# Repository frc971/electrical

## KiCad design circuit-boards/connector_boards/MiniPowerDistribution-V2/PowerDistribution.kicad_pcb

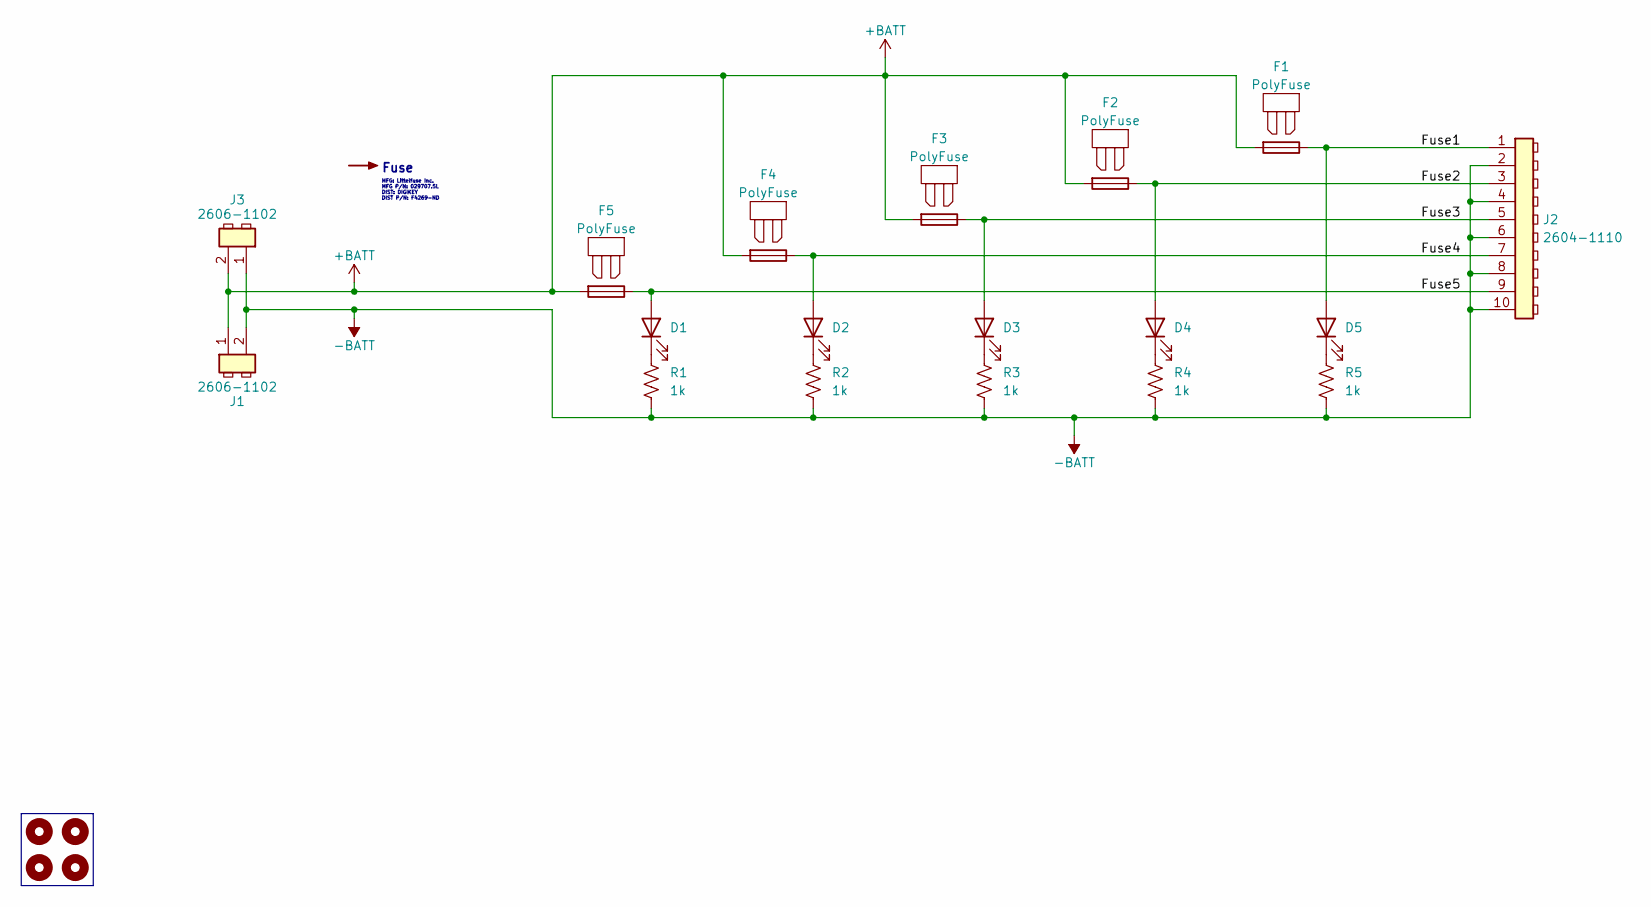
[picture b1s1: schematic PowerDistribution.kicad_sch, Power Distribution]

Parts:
D1, D2, D3, D4, D5: QTLP651C4TR; LED_1206_3216Metric_Pad1.42x1.75mm_HandSolder; MFG P/N QTLP651C4TR
F1, F2, F3, F4, F5: PolyFuse; FUSE_3568; MFG P/N 3568
H1, H2, H5, H6: MountingHole; MountingHole_2.2mm_M2_DIN965_Pad
J1, J3: 2606-1102; 2606-1102&slash_000-005; MFG P/N 2606-1102
J2: 2604-1110; MFG P/N 2604-1110
R1, R2, R3, R4, R5: 1k; R_1206_3216Metric_Pad1.30x1.75mm_HandSolder; MFG P/N RMCF1206FT1K00

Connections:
+BATT: F1.2, F2.2, F3.2, F4.2, F5.2, J1.1, J3.2
-BATT: J1.2, J2.2, J2.4, J2.6, J2.8, J2.10, J3.1, R1.2, R2.2, R3.2, R4.2, R5.2
/Fuse1: D5.2 (A), F1.1, J2.1
/Fuse2: D4.2 (A), F2.1, J2.3
/Fuse3: D3.2 (A), F3.1, J2.5
/Fuse4: D2.2 (A), F4.1, J2.7
/Fuse5: D1.2 (A), F5.1, J2.9
unnamed: D1.1 (K), R1.1
unnamed: D2.1 (K), R2.1
unnamed: D3.1 (K), R3.1
unnamed: D4.1 (K), R4.1
unnamed: D5.1 (K), R5.1

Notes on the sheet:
Fuse
MFG: Littelfuse Inc. MFG P/N: 029707.5L DIST: DIGIKEY DIST P/N: F4269-ND

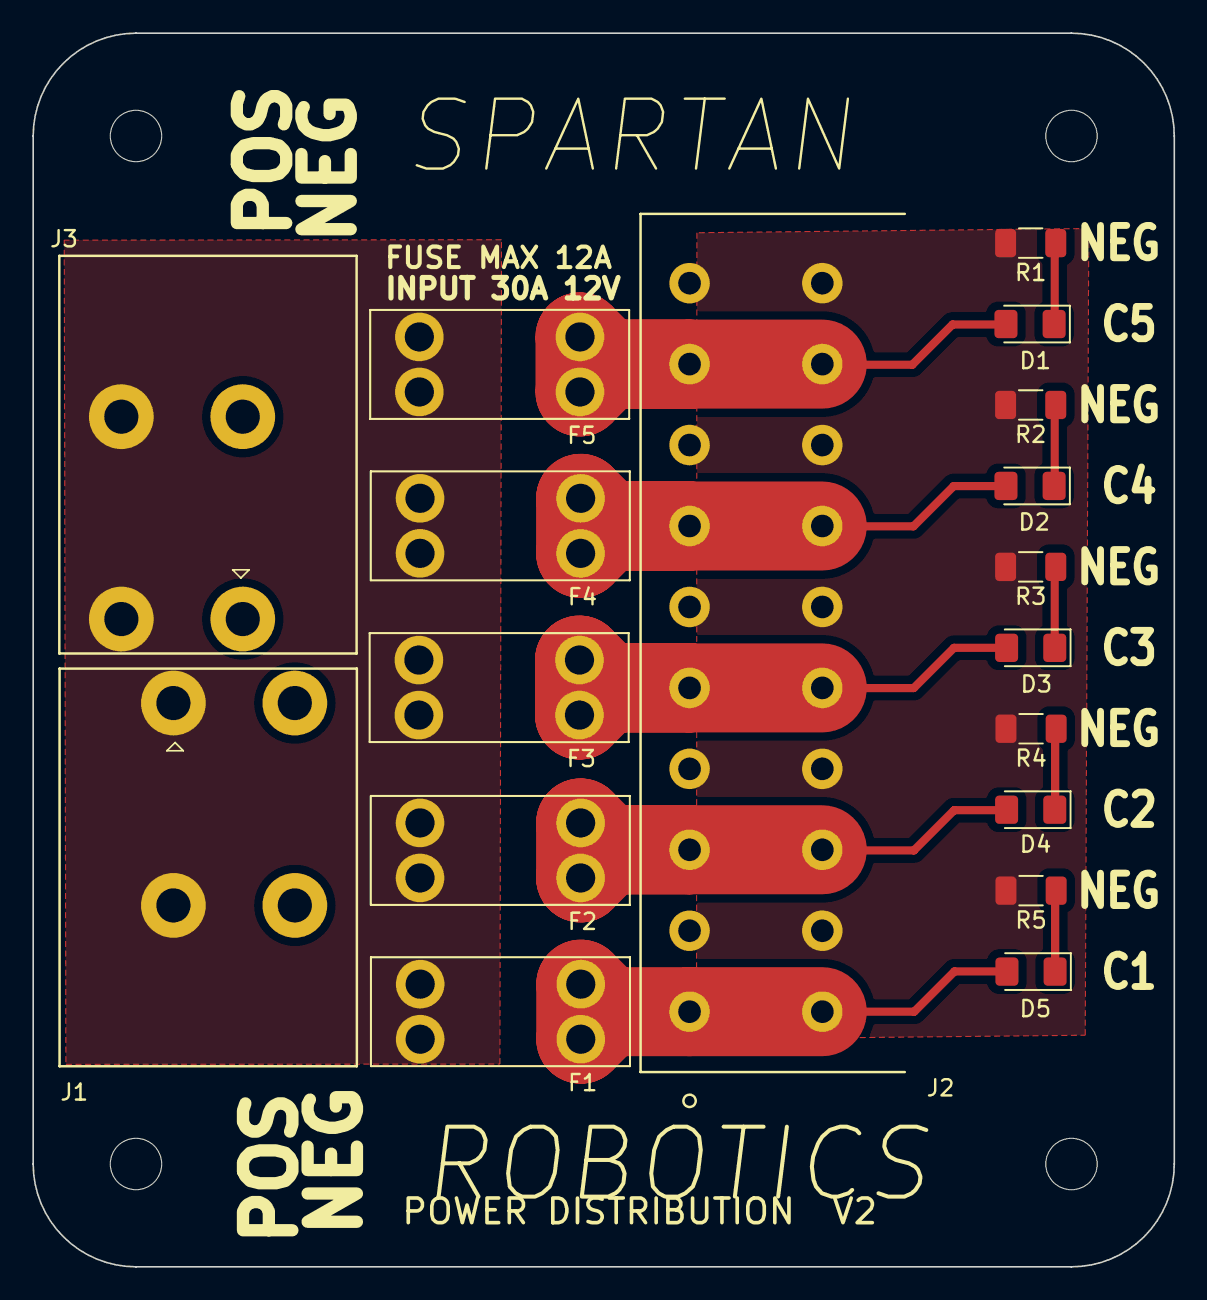
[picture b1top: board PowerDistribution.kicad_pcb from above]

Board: 2 copper layers, 70.5 x 76.2 mm, 22 parts (0 on the bottom side), 12 nets.

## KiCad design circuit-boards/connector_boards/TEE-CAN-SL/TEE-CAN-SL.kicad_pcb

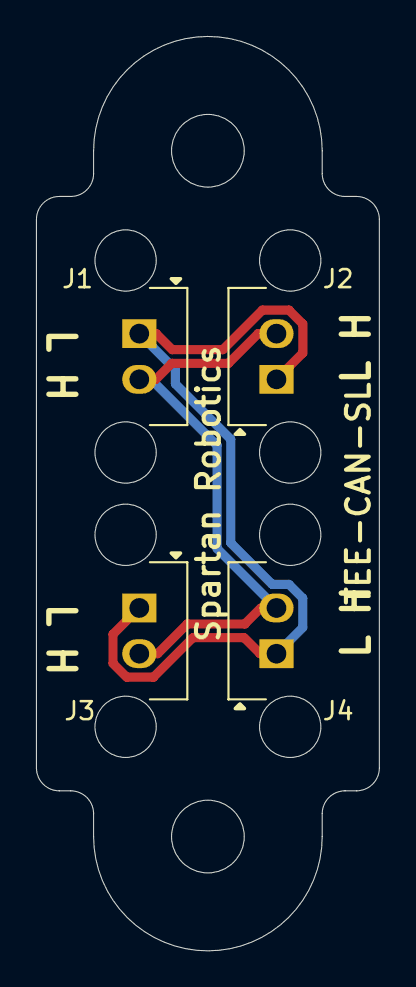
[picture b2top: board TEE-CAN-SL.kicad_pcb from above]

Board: 2 copper layers, 19.1 x 50.8 mm, 6 parts (0 on the bottom side), 2 nets.

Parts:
H1, H2: MountingHole; MountingHole_2.1mm
J1, J2, J3, J4: Conn_01x02_Pin; 70541-0036

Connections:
/CAN_H: J1.2, J2.2, J3.2, J4.2
/CAN_L: J1.1, J2.1, J3.1, J4.1

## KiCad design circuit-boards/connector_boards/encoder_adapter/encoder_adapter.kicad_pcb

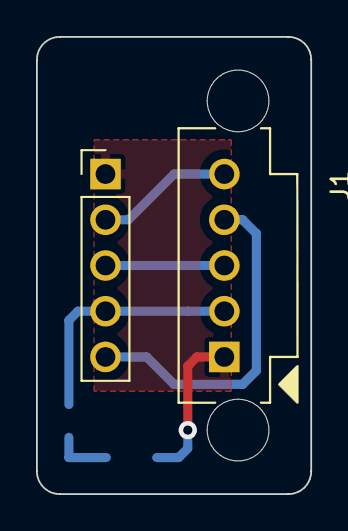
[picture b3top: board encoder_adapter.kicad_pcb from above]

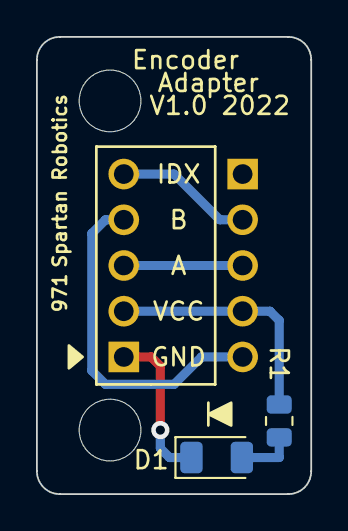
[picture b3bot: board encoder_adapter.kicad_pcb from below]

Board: 2 copper layers, 15.2 x 25.4 mm, 4 parts (2 on the bottom side), 6 nets.

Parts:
D1: LED; LED_1206_3216Metric
J1: Encoder; MOLEX_0705410074
J2: Conn_01x05_Male; PinHeader_1x05_P2.54mm_Vertical
R1: R; R_0805_2012Metric

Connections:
/A: J1.3, J2.3
/B: J1.4, J2.5
/GND: D1.1 (K), J1.1, J2.1
/IDX: J1.5, J2.2
/VCC: J1.2, J2.4, R1.1
unnamed: D1.2 (A), R1.2

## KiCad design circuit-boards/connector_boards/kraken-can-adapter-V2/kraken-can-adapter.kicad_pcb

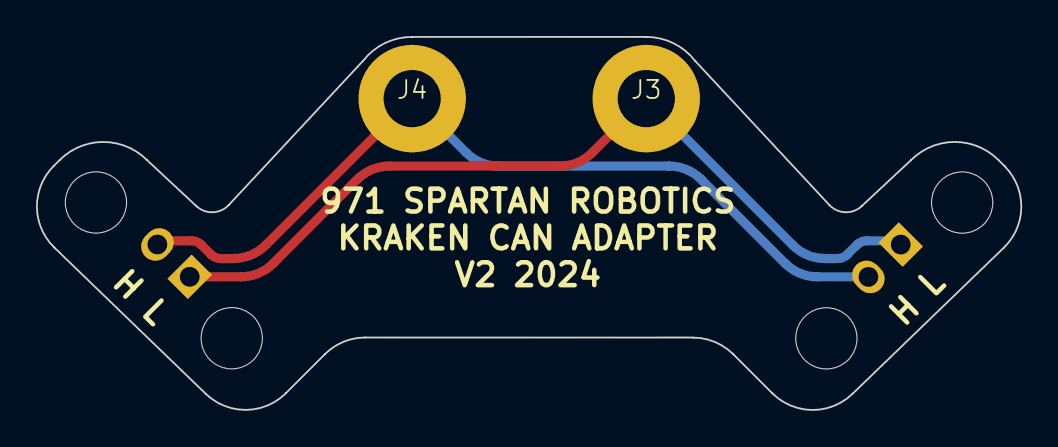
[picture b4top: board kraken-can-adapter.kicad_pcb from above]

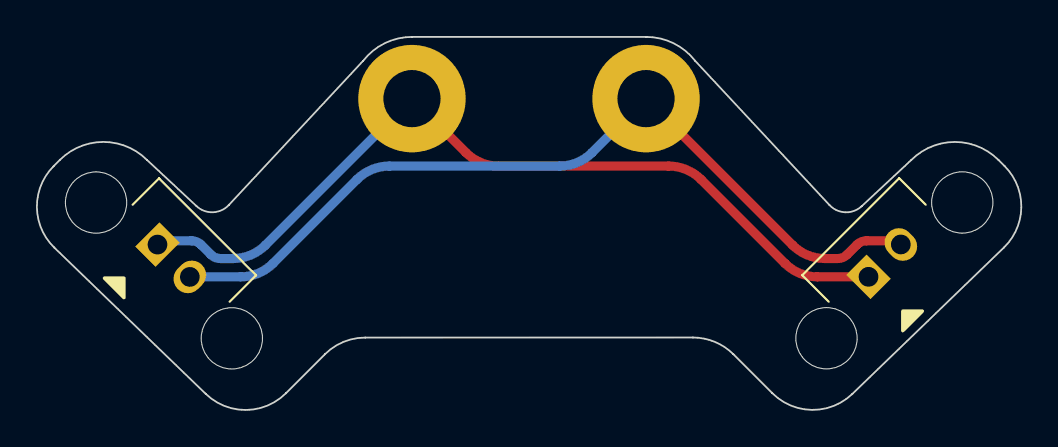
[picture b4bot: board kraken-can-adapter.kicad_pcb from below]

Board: 2 copper layers, 54.7 x 20.7 mm, 4 parts (2 on the bottom side), 2 nets.

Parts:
J1, J2: CAN; 70541-0001
J3: CAN_L; ScrewTerminal-#4
J4: CAN_H; ScrewTerminal-#4

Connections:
/CAN_H: J1.2, J2.2, J4.1
/CAN_L: J1.1, J2.1, J3.1

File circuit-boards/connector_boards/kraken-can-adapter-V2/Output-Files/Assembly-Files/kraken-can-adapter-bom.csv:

Item,QUANTITY,Reference,Value,MFG,MFG P/N,DIST,DIST P/N
1,2,"HW1,HW2",4-40 x 3/16 Steel Pan Head Torx Screw,McMaster-Carr,93701A250,,
2,2,"HW3,HW4",#4 Belleville Spring Lock Washer,McMaster-Carr,90895A121,,
3,2,"J1,J2",CAN,Molex,705450036,Digikey,WM4142-ND

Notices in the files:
parts and their libraries:
Copyright 2016 Accelerated Designs. All rights reserved.
Copyright 2021 Accelerated Designs. All rights reserved.
